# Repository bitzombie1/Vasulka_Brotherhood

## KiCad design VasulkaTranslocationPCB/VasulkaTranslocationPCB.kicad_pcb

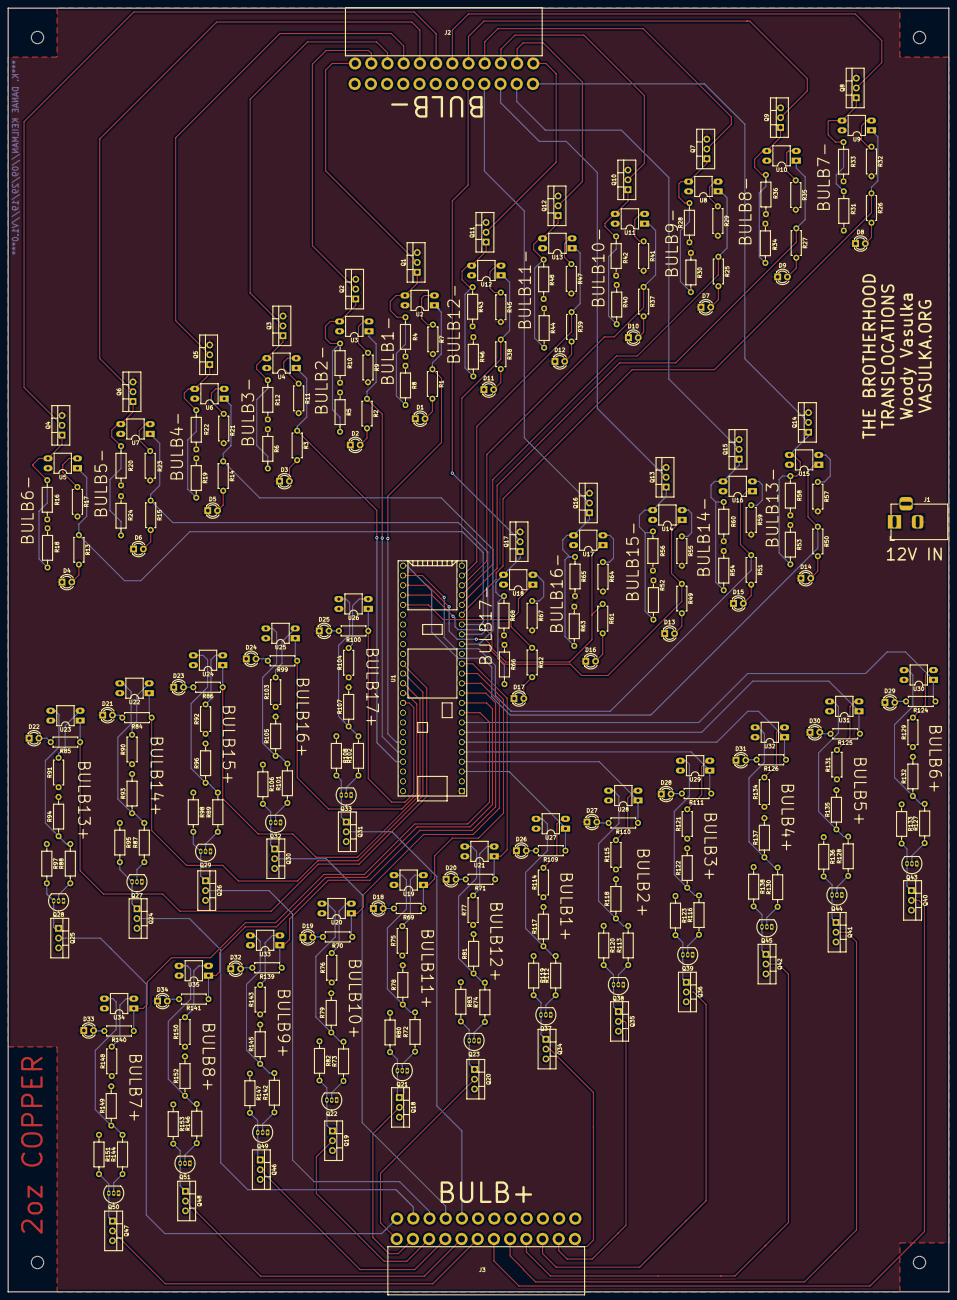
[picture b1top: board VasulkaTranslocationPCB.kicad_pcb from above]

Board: 2 copper layers, 243.8 x 332.7 mm, 280 parts (0 on the bottom side), 206 nets.

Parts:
D1, D2, D3, D4, D5, D6, D7, D8, D9, D10, D11, D12, D13, D14, D15, D16, D17, D18, D19, D20, D21, D22, D23, D24, D25, D26, D27, D28, D29, D30, D31, D32, D33, D34: LED; LED_D3.0mm
J1: Barrel_Jack; BarrelJack_Horizontal
J2: BULB-; CONN02x12
J3: BULB+; CONN02x12
MH1, MH2, MH3, MH4: MountingHole; MountingHole_3.2mm_M3
Q1, Q2, Q3, Q4, Q5, Q6, Q7, Q8, Q9, Q10, Q11, Q12, Q13, Q14, Q15, Q16, Q17: IRF510; TO-220-3_Vertical
Q18, Q19, Q20, Q24, Q25, Q26, Q30, Q31, Q34, Q35, Q36, Q40, Q41, Q42, Q46, Q47, Q48: IRF9520; TO-220-3_Vertical
Q21, Q22, Q23, Q27, Q28, Q29, Q32, Q33, Q37, Q38, Q39, Q43, Q44, Q45, Q49, Q50, Q51: 2N3904; TO-92_Inline_Narrow_Oval
R1, R2, R3, R13, R14, R15, R25, R26, R27, R37, R38, R39, R49, R50, R51, R61, R62: 1.8K; R_Axial_DIN0207_L6.3mm_D2.5mm_P7.62mm_Horizontal
R4, R5, R6, R8, R10, R12, R16, R18, R19, R20, R22, R24, R28, R30, R31, R33, R34, R36, R40, R42, R43, R44, R46, R48, R52, R53, R54, R56, R58, R60, R63, R65, R66, R68, R72, R73, R74, R78, R79, R80, R81, R82, R83, R87, R88, R89, R93, R94, R95, R96, R97, R98, R101, R102, R105, R106, R107, R108, R112, R113, R116, R117, R118, R119, R120, R122, R123, R127, R128, R130, R132, R133, R135, R136, R137, R138, R142, R144, R145, R146, R147, R149, R151, R152, R153: 10K; R_Axial_DIN0207_L6.3mm_D2.5mm_P10.16mm_Horizontal
R7, R9, R11, R17, R21, R23, R29, R32, R35, R41, R45, R47, R55, R57, R59, R64, R67, R75, R76, R77, R90, R91, R92, R103, R104, R114, R115, R121, R129, R131, R134, R143, R148, R150: 430; R_Axial_DIN0207_L6.3mm_D2.5mm_P7.62mm_Horizontal
R69, R70, R71, R84, R85, R86, R99, R100, R109, R110, R111, R124, R125, R126, R139, R140, R141: 1.8k; R_Axial_DIN0207_L6.3mm_D2.5mm_P7.62mm_Horizontal
U1: TEENSY_3.5; TEENSY_3.5_3.6_NO_SILK_MINIMAL
U2, U3, U4, U5, U6, U7, U8, U9, U10, U11, U12, U13, U14, U15, U16, U17, U18, U19, U20, U21, U22, U23, U24, U25, U26, U27, U28, U29, U30, U31, U32, U33, U34, U35: VO618A-4; DIP-4_W7.62mm_LongPads

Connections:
+1: J3.1, Q34.2
+2: J3.2, Q35.2
+3: J3.3, Q36.2
+4: J3.4, Q42.2
+5: J3.5, Q41.2
+6: J3.6, Q40.2
+7: J3.7, Q47.2
+8: J3.8, Q48.2
+9: J3.9, Q46.2
+10: J3.10, Q19.2
+11: J3.11, Q18.2
+12: J3.12, Q20.2
+12V: J1.1, Q18.3, Q19.3, Q20.3, Q24.3, Q25.3, Q26.3, Q30.3, Q31.3, Q34.3, Q35.3, Q36.3, Q40.3, Q41.3, Q42.3, Q46.3, Q47.3, Q48.3, R80.1, R82.1, R83.1, R95.1, R97.1, R98.1, R106.1, R108.1, R119.1, R120.1, R123.1, R133.1, R136.1, R138.1, R147.1, R151.1, R153.1, U2.4, U3.4, U4.4, U5.4, U6.4, U7.4, U8.4, U9.4, U10.4, U11.4, U12.4, U13.4, U14.4, U15.4, U16.4, U17.4, U18.4, U19.4, U20.4, U21.4, U22.4, U23.4, U24.4, U25.4, U26.4, U27.4, U28.4, U29.4, U30.4, U31.4, U32.4, U33.4, U34.4, U35.4
+13: J3.13, Q25.2
+14: J3.14, Q24.2
+15: J3.15, Q26.2
+16: J3.16, Q30.2
+17: J3.17, Q31.2
-1: J2.1, Q1.2
-2: J2.2, Q2.2
-3: J2.3, Q3.2
-4: J2.4, Q5.2
-5: J2.5, Q6.2
-6: J2.6, Q4.2
-7: J2.7, Q8.2
-8: J2.8, Q9.2
-9: J2.9, Q7.2
-10: J2.10, Q10.2
-11: J2.11, Q12.2
-12: J2.12, Q11.2
-13: J2.13, Q14.2
-14: J2.14, Q15.2
-15: J2.15, Q13.2
-16: J2.16, Q16.2
-17: J2.17, Q17.2
GND: D1.1, D2.1, D3.1, D4.1, D5.1, D6.1, D7.1, D8.1, D9.1, D10.1, D11.1, D12.1, D13.1, D14.1, D15.1, D16.1, D17.1, D18.1, D19.1, D20.1, D21.1, D22.1, D23.1, D24.1, D25.1, D26.1, D27.1, D28.1, D29.1, D30.1, D31.1, D32.1, D33.1, D34.1, J1.2, Q1.3, Q2.3, Q3.3, Q4.3, Q5.3, Q6.3, Q7.3, Q8.3, Q9.3, Q10.3, Q11.3, Q12.3, Q13.3, Q14.3, Q15.3, Q16.3, Q17.3, Q21.1, Q22.1, Q23.1, Q27.1, Q28.1, Q29.1, Q32.1, Q33.1, Q37.1, Q38.1, Q39.1, Q43.1, Q44.1, Q45.1, Q49.1, Q50.1, Q51.1, R4.1, R5.1, R6.1, R7.2, R8.1, R9.2, R10.1, R11.2, R12.1, R16.1, R17.2, R18.1, R19.1, R20.1, R21.2, R22.1, R23.2, R24.1, R28.1, R29.2, R30.1, R31.1, R32.2, R33.1, R34.1, R35.2, R36.1, R40.1, R41.2, R42.1, R43.1, R44.1, R45.2, R46.1, R47.2, R48.1, R52.1, R53.1, R54.1, R55.2, R56.1, R57.2, R58.1, R59.2, R60.1, R63.1, R64.2, R65.1, R66.1, R67.2, R68.1, R75.1, R76.1, R77.1, R78.2, R79.2, R81.2, R90.1, R91.1, R92.1, R93.2, R94.2, R96.2, R103.1, R104.1, R105.2, R107.2, R114.1, R115.1, R117.2, R118.2, R121.1, R122.2, R129.1, R131.1, R132.2, R134.1, R135.2, R137.2, R143.1, R145.2, R148.1, R149.2, R150.1, R152.2, U1.1
unnamed: D1.2, R1.2
unnamed: D2.2, R2.2
unnamed: D3.2, R3.2
unnamed: D4.2, R13.2
unnamed: D5.2, R14.2
unnamed: D6.2, R15.2
unnamed: D7.2, R25.2
unnamed: D8.2, R26.2
unnamed: D9.2, R27.2
unnamed: D10.2, R37.2
unnamed: D11.2, R38.2
unnamed: D12.2, R39.2
unnamed: D13.2, R49.2
unnamed: D14.2, R50.2
unnamed: D15.2, R51.2
unnamed: D16.2, R61.2
unnamed: D17.2, R62.2
unnamed: D18.2, R69.2
unnamed: D19.2, R70.2
unnamed: D20.2, R71.2
unnamed: D21.2, R84.2
unnamed: D22.2, R85.2
unnamed: D23.2, R86.2
unnamed: D24.2, R99.2
unnamed: D25.2, R100.2
unnamed: D26.2, R109.2
unnamed: D27.2, R110.2
unnamed: D28.2, R111.2
unnamed: D29.2, R124.2
unnamed: D30.2, R125.2
unnamed: D31.2, R126.2
unnamed: D32.2, R139.2
unnamed: D33.2, R140.2
unnamed: D34.2, R141.2
unnamed: Q1.1, R4.2, R8.2, U2.3
unnamed: Q2.1, R5.2, R10.2, U3.3
unnamed: Q3.1, R6.2, R12.2, U4.3
unnamed: Q4.1, R16.2, R18.2, U5.3
unnamed: Q5.1, R19.2, R22.2, U6.3
unnamed: Q6.1, R20.2, R24.2, U7.3
unnamed: Q7.1, R28.2, R30.2, U8.3
unnamed: Q8.1, R31.2, R33.2, U9.3
unnamed: Q9.1, R34.2, R36.2, U10.3
unnamed: Q10.1, R40.2, R42.2, U11.3
unnamed: Q11.1, R43.2, R46.2, U12.3
unnamed: Q12.1, R44.2, R48.2, U13.3
unnamed: Q13.1, R52.2, R56.2, U14.3
unnamed: Q14.1, R53.2, R58.2, U15.3
unnamed: Q15.1, R54.2, R60.2, U16.3
unnamed: Q16.1, R63.2, R65.2, U17.3
unnamed: Q17.1, R66.2, R68.2, U18.3
unnamed: Q18.1, Q21.3, R80.2
unnamed: Q19.1, Q22.3, R82.2
unnamed: Q20.1, Q23.3, R83.2
unnamed: Q21.2, R72.1
unnamed: Q22.2, R73.1
unnamed: Q23.2, R74.1
unnamed: Q24.1, Q27.3, R95.2
unnamed: Q25.1, Q28.3, R97.2
unnamed: Q26.1, Q29.3, R98.2
unnamed: Q27.2, R87.1
unnamed: Q28.2, R88.1
unnamed: Q29.2, R89.1
unnamed: Q30.1, Q32.3, R106.2
unnamed: Q31.1, Q33.3, R108.2
unnamed: Q32.2, R101.1
unnamed: Q33.2, R102.1
unnamed: Q34.1, Q37.3, R119.2
unnamed: Q35.1, Q38.3, R120.2
unnamed: Q36.1, Q39.3, R123.2
unnamed: Q37.2, R112.1
unnamed: Q38.2, R113.1
unnamed: Q39.2, R116.1
unnamed: Q40.1, Q43.3, R133.2
unnamed: Q41.1, Q44.3, R136.2
unnamed: Q42.1, Q45.3, R138.2
unnamed: Q43.2, R127.1
unnamed: Q44.2, R128.1
unnamed: Q45.2, R130.1
unnamed: Q46.1, Q49.3, R147.2
unnamed: Q47.1, Q50.3, R151.2
unnamed: Q48.1, Q51.3, R153.2
unnamed: Q49.2, R142.1
unnamed: Q50.2, R144.1
unnamed: Q51.2, R146.1
unnamed: R7.1, U2.2
unnamed: R9.1, U3.2
unnamed: R11.1, U4.2
unnamed: R17.1, U5.2
unnamed: R21.1, U6.2
unnamed: R23.1, U7.2
unnamed: R29.1, U8.2
unnamed: R32.1, U9.2
unnamed: R35.1, U10.2
unnamed: R41.1, U11.2
unnamed: R45.1, U12.2
unnamed: R47.1, U13.2
unnamed: R55.1, U14.2
unnamed: R57.1, U15.2
unnamed: R59.1, U16.2
unnamed: R64.1, U17.2
unnamed: R67.1, U18.2
unnamed: R72.2, R78.1, U19.3
unnamed: R73.2, R79.1, U20.3
unnamed: R74.2, R81.1, U21.3
unnamed: R75.2, U19.2
unnamed: R76.2, U20.2
unnamed: R77.2, U21.2
unnamed: R87.2, R93.1, U22.3
unnamed: R88.2, R94.1, U23.3
unnamed: R89.2, R96.1, U24.3
unnamed: R90.2, U22.2
unnamed: R91.2, U23.2
unnamed: R92.2, U24.2
unnamed: R101.2, R105.1, U25.3
unnamed: R102.2, R107.1, U26.3
unnamed: R103.2, U25.2
unnamed: R104.2, U26.2
unnamed: R112.2, R117.1, U27.3
unnamed: R113.2, R118.1, U28.3
unnamed: R114.2, U27.2
unnamed: R115.2, U28.2
unnamed: R116.2, R122.1, U29.3
unnamed: R121.2, U29.2
unnamed: R127.2, R132.1, U30.3
unnamed: R128.2, R135.1, U31.3
unnamed: R129.2, U30.2
unnamed: R130.2, R137.1, U32.3
unnamed: R131.2, U31.2
unnamed: R134.2, U32.2
unnamed: R142.2, R145.1, U33.3
unnamed: R143.2, U33.2
unnamed: R144.2, R149.1, U34.3
unnamed: R146.2, R152.1, U35.3
unnamed: R148.2, U34.2
unnamed: R150.2, U35.2
PIN1: R109.1, U1.3, U27.1
PIN2: R110.1, U1.4, U28.1
PIN3: R111.1, U1.5, U29.1
PIN4: R126.1, U1.6, U32.1
PIN5: R125.1, U1.7, U31.1
PIN6: R124.1, U1.8, U30.1
PIN7: R140.1, U1.9, U34.1
PIN8: R141.1, U1.10, U35.1
PIN9: R139.1, U1.11, U33.1
PIN10: R70.1, U1.12, U20.1
PIN11: R69.1, U1.13, U19.1
PIN12: R71.1, U1.14, U21.1
PIN13: R85.1, U1.40, U23.1
PIN14: R84.1, U1.41, U22.1
PIN15: R86.1, U1.42, U24.1
PIN16: R99.1, U1.43, U25.1
PIN17: R100.1, U1.44, U26.1
PIN21: R1.1, U1.48, U2.1
PIN22: R2.1, U1.49, U3.1
PIN23: R3.1, U1.50, U4.1
PIN24: R14.1, U1.16, U6.1
PIN25: R15.1, U1.17, U7.1
PIN26: R13.1, U1.18, U5.1
PIN27: R26.1, U1.19, U9.1
PIN28: R27.1, U1.20, U10.1
PIN29: R25.1, U1.21, U8.1
PIN30: R37.1, U1.22, U11.1
PIN31: R39.1, U1.23, U13.1
PIN32: R38.1, U1.24, U12.1
PIN33: R50.1, U1.30, U15.1
PIN34: R51.1, U1.31, U16.1
PIN35: R49.1, U1.32, U14.1
PIN36: R61.1, U1.33, U17.1
PIN37: R62.1, U1.34, U18.1

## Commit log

2019-02-24 added folders
2019-02-24 more files
2019-02-25 stuff
2019-02-25 more
2019-05-11 autom
2020-02-04 PCB Added
2020-02-25 CHANGED graphics
2020-05-11 New BOM
2020-05-12 INVENTORY ADDED
2020-05-14 Inventory PDF
2021-02-19 Inventory
